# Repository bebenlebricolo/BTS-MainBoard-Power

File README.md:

# BTS-MainBoard-Power
Beer thermoregulation system mainboard  - power section

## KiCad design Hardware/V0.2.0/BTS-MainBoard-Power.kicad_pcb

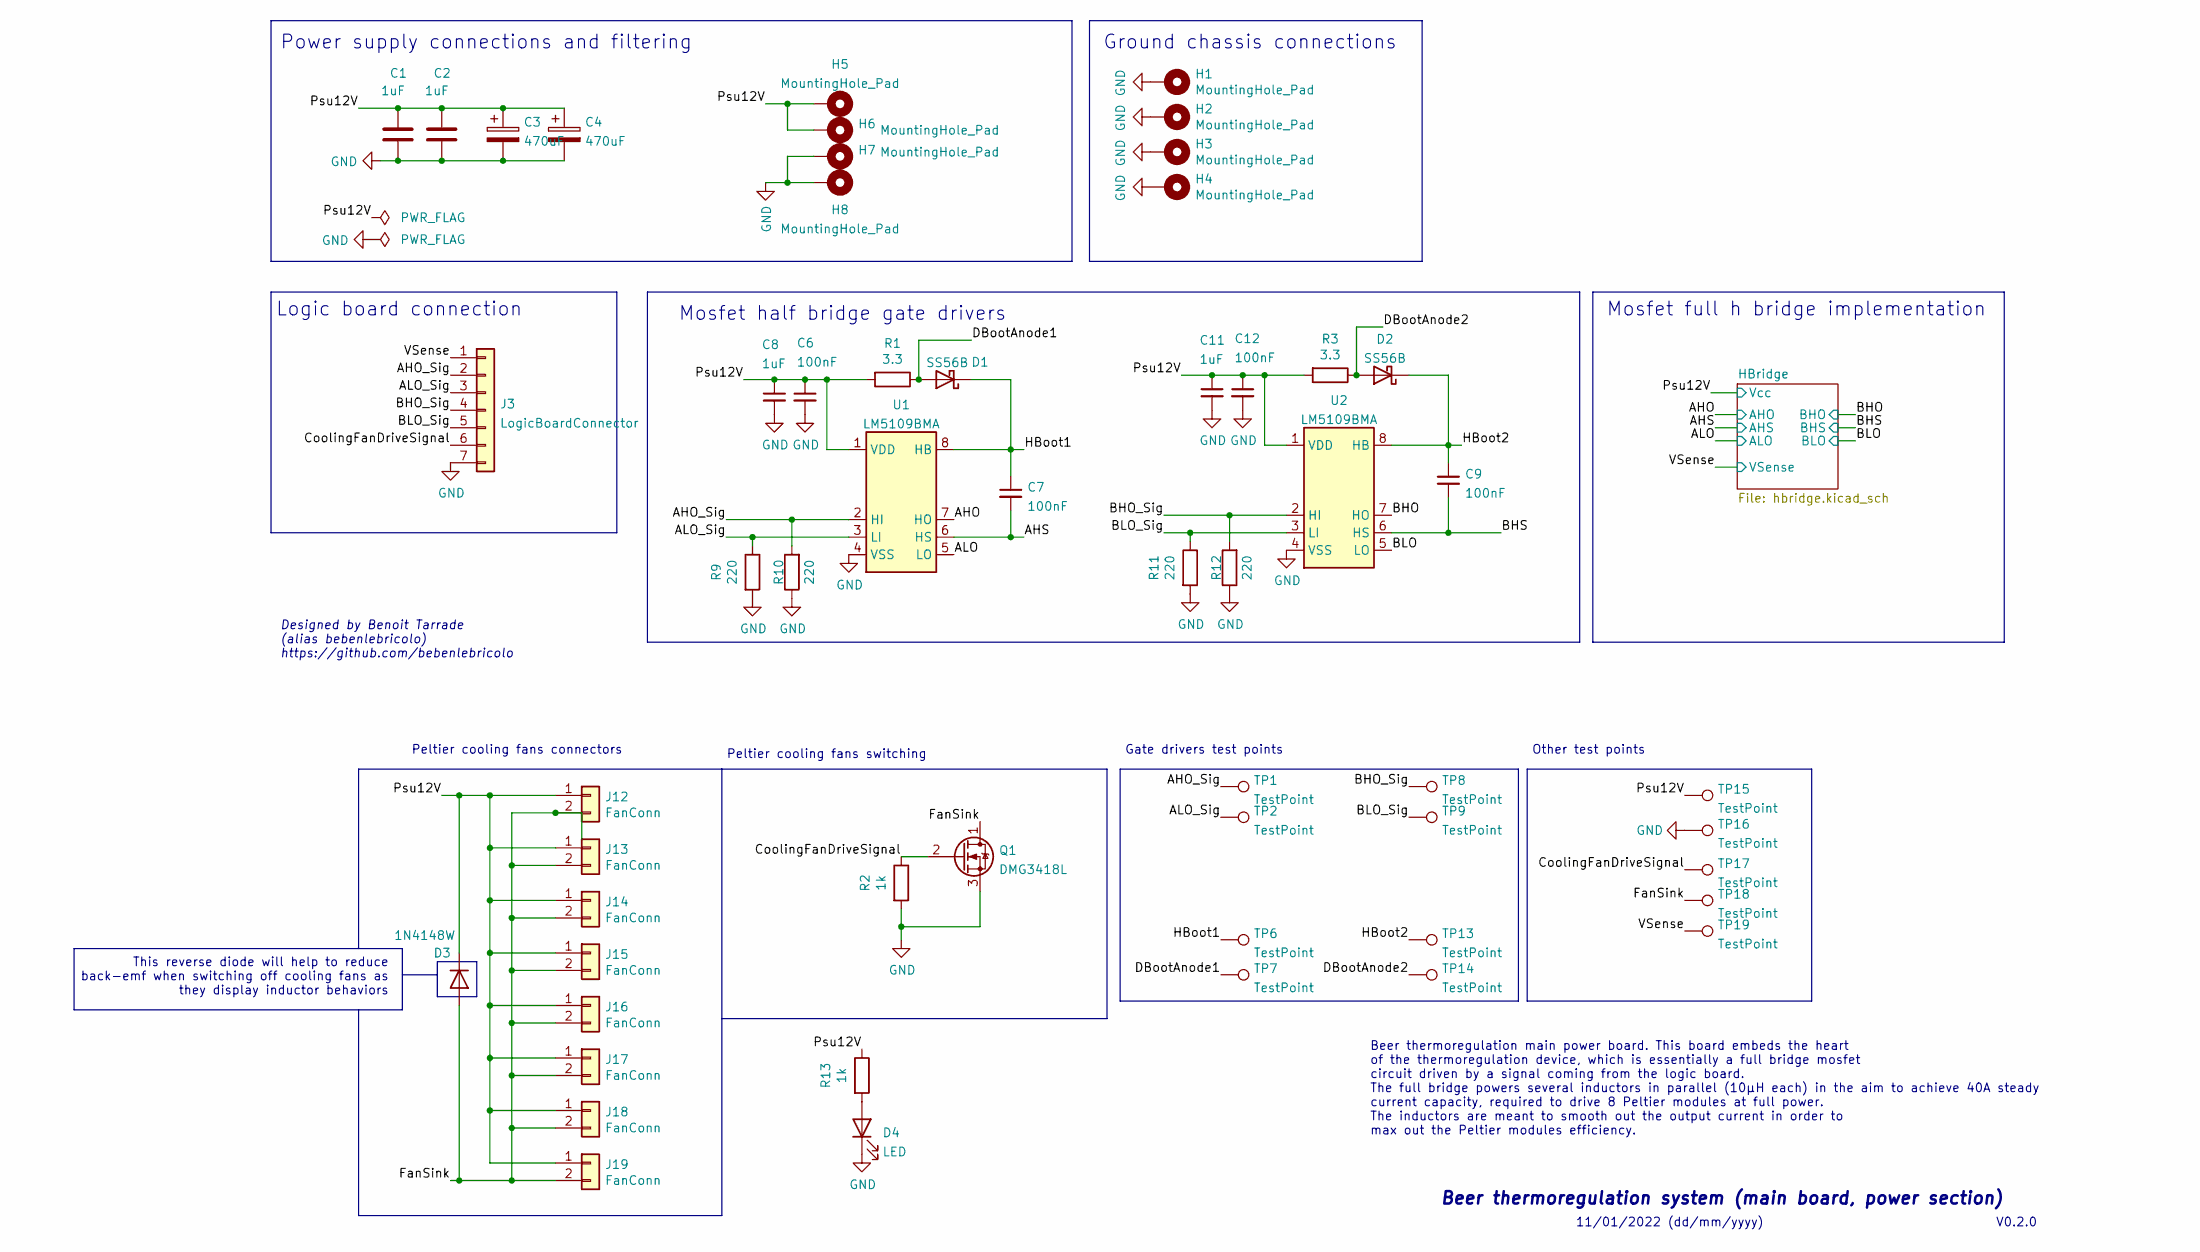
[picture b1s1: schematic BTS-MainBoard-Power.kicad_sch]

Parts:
C1, C2, C8, C11: 1uF; C_1206_3216Metric_Pad1.33x1.80mm_HandSolder
C3, C4: 470uF; CP_Elec_10x10
C6, C7, C9, C12: 100nF; C_1206_3216Metric_Pad1.33x1.80mm_HandSolder
D1, D2: SS56B
D3: 1N4148W; D_SOD-123
D4: LED; D_0805_2012Metric
H1, H2, H3, H4: MountingHole_Pad; MountingHole_4mm_Pad_Via
H5, H6, H7, H8: MountingHole_Pad; MountingHole_3mm_Pad_Via
J3: LogicBoardConnector; PinHeader_1x07_P2.54mm_Vertical
J12, J13, J14, J15, J16, J17, J18, J19: FanConn; PinSocket_1x02_P2.54mm_Vertical
Q1: DMG3418L; SOT-23
R1, R3: 3.3; R_1206_3216Metric_Pad1.30x1.75mm_HandSolder
R2, R13: 1k; R_1206_3216Metric_Pad1.30x1.75mm_HandSolder
R9, R10, R11, R12: 220; R_1206_3216Metric_Pad1.30x1.75mm_HandSolder
TP1, TP2, TP6, TP7, TP8, TP9, TP13, TP14, TP15, TP16, TP17, TP18, TP19: TestPoint; TestPoint_Pad_D1.0mm
U1, U2: LM5109BMA; SOIC-8_3.9x4.9mm_P1.27mm

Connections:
/AHO: U1.7 (HO); also elsewhere on the board
/AHO_Sig: J3.2, R10.2, TP1.1, U1.2 (HI)
/AHS: C7.2, U1.6 (HS); also elsewhere on the board
/ALO: U1.5 (LO); also elsewhere on the board
/ALO_Sig: J3.3, R9.1, TP2.1, U1.3 (LI)
/BHO: U2.7 (HO); also elsewhere on the board
/BHO_Sig: J3.4, R12.2, TP8.1, U2.2 (HI)
/BHS: C9.2, U2.6 (HS); also elsewhere on the board
/BLO: U2.5 (LO); also elsewhere on the board
/BLO_Sig: J3.5, R11.1, TP9.1, U2.3 (LI)
/CoolingFanDriveSignal: J3.6, Q1.2 (G), R2.1, TP17.1
/DBootAnode1: D1.2 (A), R1.1, TP7.1
/DBootAnode2: D2.2 (A), R3.1, TP14.1
/FanSink: D3.2 (A), J12.2, J13.2, J14.2, J15.2, J16.2, J17.2, J18.2, J19.2, Q1.1 (D), TP18.1
/HBoot1: C7.1, D1.1 (K), TP6.1, U1.8 (HB)
/HBoot2: C9.1, D2.1 (K), TP13.1, U2.8 (HB)
/Psu12V: C1.1, C2.1, C3.1, C4.1, C6.1, C8.1, C11.1, C12.1, D3.1 (K), H5.1, H6.1, J12.1, J13.1, J14.1, J15.1, J16.1, J17.1, J18.1, J19.1, R1.2, R3.2, R13.1, TP15.1, U1.1 (VDD), U2.1 (VDD); also elsewhere on the board
/VSense: J3.1, TP19.1; also elsewhere on the board
GND: C1.2, C2.2, C3.2, C4.2, C6.2, C8.2, C11.2, C12.2, D4.1 (K), H1.1, H2.1, H3.1, H4.1, H7.1, H8.1, J3.7, Q1.3 (S), R2.2, R9.2, R10.1, R11.2, R12.1, TP16.1, U1.4 (VSS), U2.4 (VSS); also elsewhere on the board
unnamed: D4.2 (A), R13.2

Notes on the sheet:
Peltier cooling fans connectors
Gate drivers test points
Logic board connection
Other test points
This reverse diode will help to reduce back-emf when switching off cooling fans as they display inductor behaviors
Mosfet half bridge gate drivers
Designed by Benoit Tarrade (alias bebenlebricolo) https://github.com/bebenlebricolo
11/01/2022 (dd/mm/yyyy)
Ground chassis connections
Peltier cooling fans switching
Mosfet full h bridge implementation
Power supply connections and filtering
V0.2.0
Beer thermoregulation main power board. This board embeds the heart of the thermoregulation device, which is essentially a full bridge mosfet circuit driven by a signal coming from the logic board. The full bridge powers several inductors in parallel (10µH each) in the aim to achieve 40A steady cur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
Beer thermoregulation system (main board, power section)

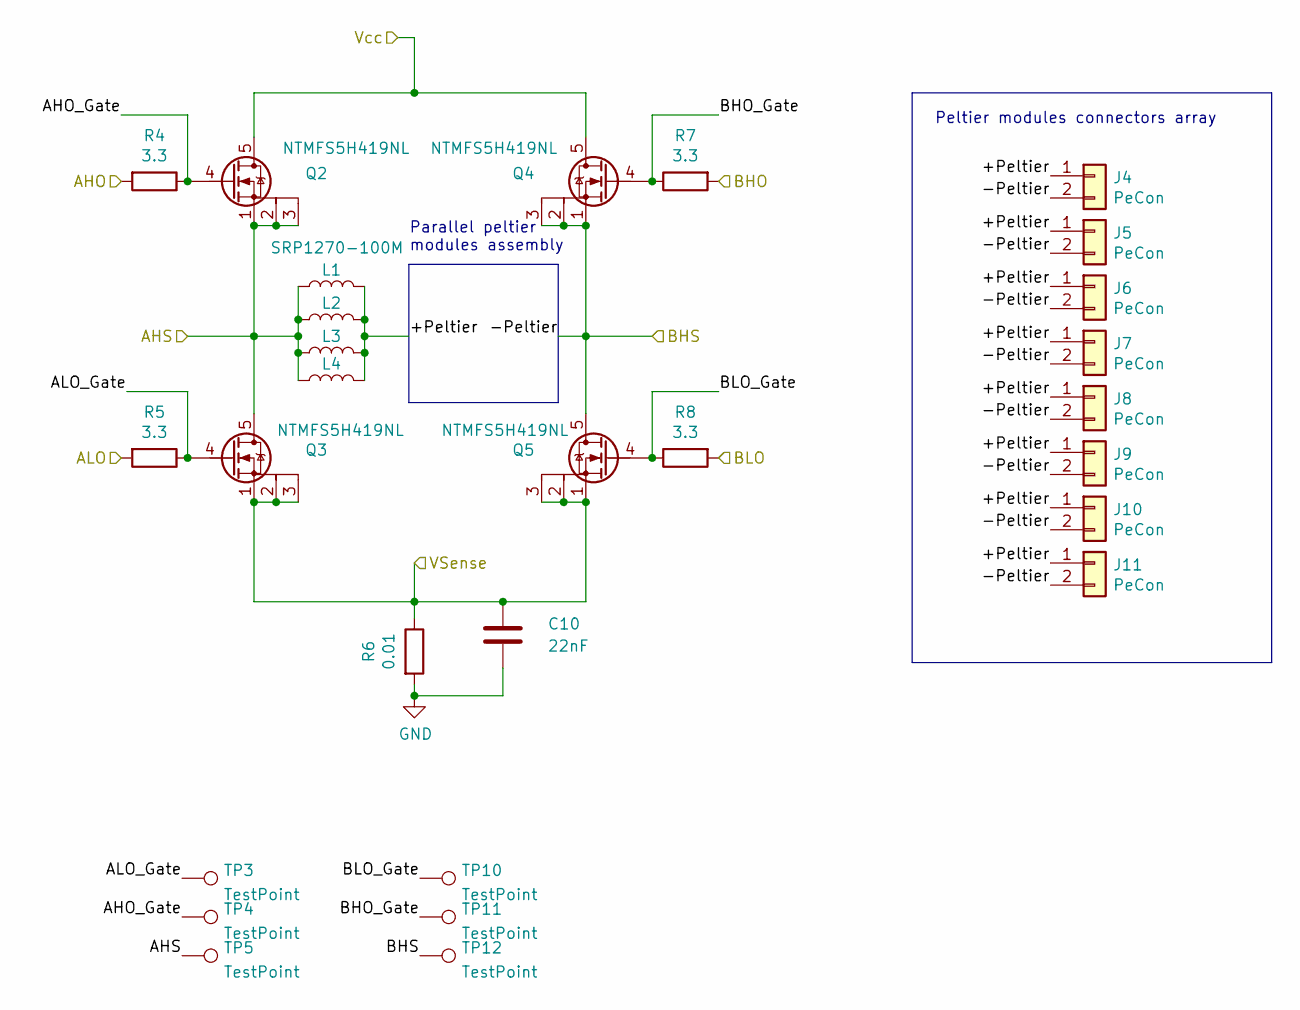
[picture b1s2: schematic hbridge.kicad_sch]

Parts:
C10: 22nF; C_1210_3225Metric_Pad1.33x2.70mm_HandSolder
J4, J5, J6, J7, J8, J9, J10, J11: PeCon; TE_1-1123723-2_1x02_P3.96mm_8Amps_Vertical
L1, L2, L3, L4: SRP1270-100M; L_Bourns_SRP1270
Q2, Q3, Q4, Q5: NTMFS5H419NL; NTMFS5G419NL
R4, R5, R7, R8: 3.3; R_1206_3216Metric_Pad1.30x1.75mm_HandSolder
R6: 0.01; R_2512_6332Metric_Pad1.40x3.35mm_HandSolder
TP3, TP4, TP5, TP10, TP11, TP12: TestPoint; TestPoint_Pad_D1.0mm

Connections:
/AHO: R4.2; also elsewhere on the board
/AHS: L1.1, L2.1, L3.1, L4.1, Q2.1 (S), Q2.2 (S), Q2.3 (S), Q3.5 (D), TP5.1; also elsewhere on the board
/ALO: R5.2; also elsewhere on the board
/BHO: R7.2; also elsewhere on the board
/BHS: J4.2, J5.2, J6.2, J7.2, J8.2, J9.2, J10.2, J11.2, Q4.1 (S), Q4.2 (S), Q4.3 (S), Q5.5 (D), TP12.1; also elsewhere on the board
/BLO: R8.2; also elsewhere on the board
/HBridge/+Peltier: J4.1, J5.1, J6.1, J7.1, J8.1, J9.1, J10.1, J11.1, L1.2, L2.2, L3.2, L4.2
/HBridge/AHO_Gate: Q2.4 (G), R4.1, TP4.1
/HBridge/ALO_Gate: Q3.4 (G), R5.1, TP3.1
/HBridge/BHO_Gate: Q4.4 (G), R7.1, TP11.1
/HBridge/BLO_Gate: Q5.4 (G), R8.1, TP10.1
/Psu12V: Q2.5 (D), Q4.5 (D); also elsewhere on the board
/VSense: C10.1, Q3.1 (S), Q3.2 (S), Q3.3 (S), Q5.1 (S), Q5.2 (S), Q5.3 (S), R6.1; also elsewhere on the board
GND: C10.2, R6.2; also elsewhere on the board

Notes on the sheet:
Parallel peltier modules assembly
Peltier modules connectors array

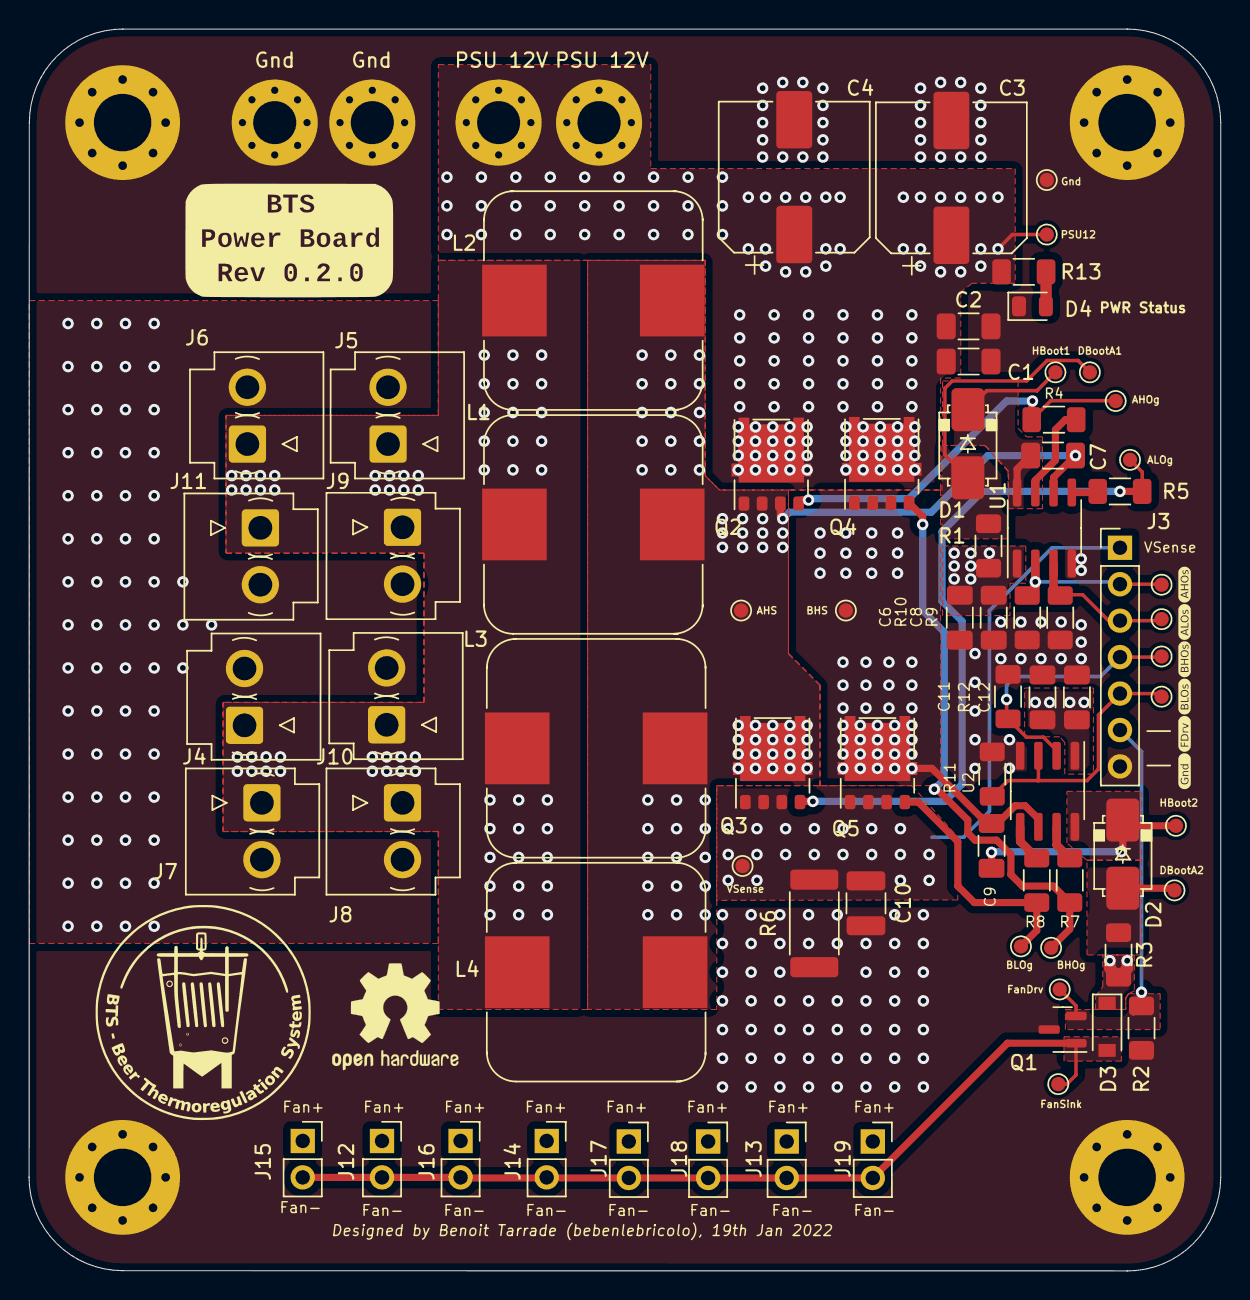
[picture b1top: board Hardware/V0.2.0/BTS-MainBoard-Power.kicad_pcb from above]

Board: 4 copper layers, 83.0 x 86.5 mm, 83 parts (0 on the bottom side), 25 nets.

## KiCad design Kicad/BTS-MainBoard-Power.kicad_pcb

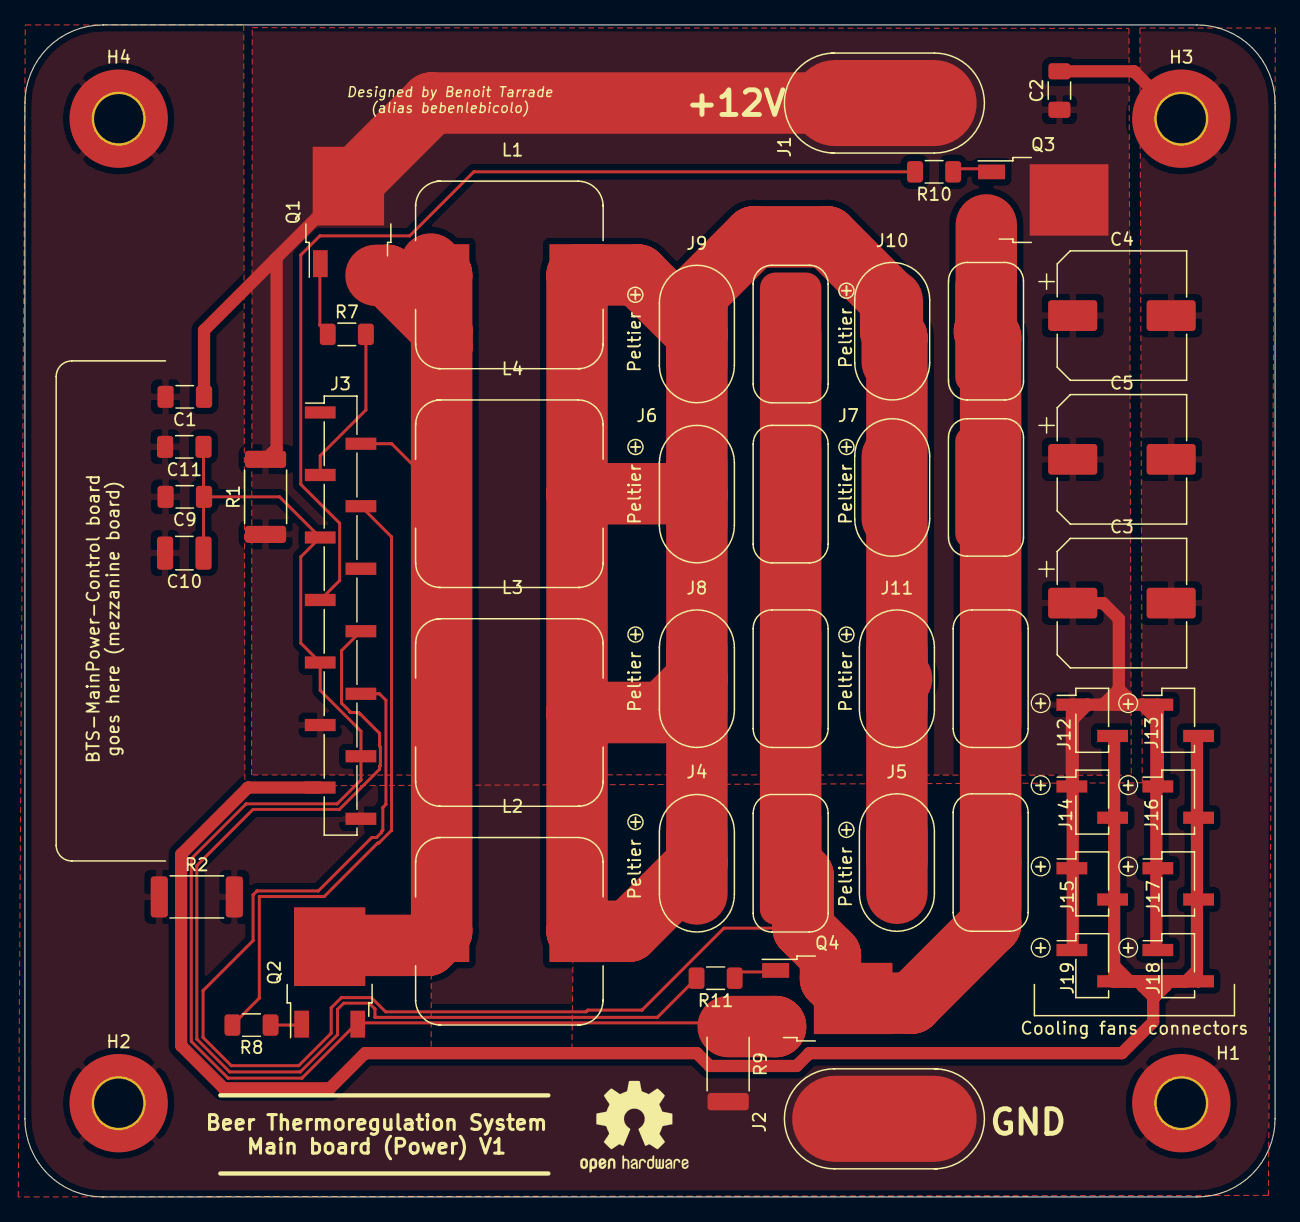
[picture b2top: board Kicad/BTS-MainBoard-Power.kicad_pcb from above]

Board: 2 copper layers, 101.6 x 95.3 mm, 46 parts (0 on the bottom side), 15 nets.

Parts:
C1, C2: 100nF; C_1206_3216Metric_Pad1.33x1.80mm_HandSolder
C3, C4, C5: 470uF; CP_Elec_10x10
C9, C11: 1nF; C_1206_3216Metric_Pad1.33x1.80mm_HandSolder
C10: 22nF; C_1210_3225Metric_Pad1.33x2.70mm_HandSolder
H1, H2, H3, H4: MountingHole_Pad; MountingHole_4mm_Pad_TopOnly
J1: +12VIn; Power_Solder_Pad_7x15mm
J2: GNDIn; Power_Solder_Pad_7x15mm
J3: Conn_01x14; PinHeader_1x14_P2.54mm_Vertical_SMD_Pin1Left
J4, J5, J6, J7, J8, J9, J10, J11: Conn_01x02; Power_Solder_Pad_5x10mm_02
J12, J13, J14, J15, J16, J17, J18, J19: Conn_01x02; PinHeader_1x02_P2.54mm_Vertical_SMD_Pin1Left
L1, L2, L3, L4: SRP1270-100M; L_Bourns_SRP1270
Q1, Q2, Q3, Q4: STD80N6F6; TO-252-2
R1, R2: 0; R_2512_6332Metric_Pad1.40x3.35mm_HandSolder
R7, R8, R10, R11: 3.3; R_1206_3216Metric_Pad1.30x1.75mm_HandSolder
R9: 0.01; R_2512_6332Metric_Pad1.40x3.35mm_HandSolder

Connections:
+12V: C1.1, C2.1, C3.1, C4.1, C5.1, J1.1, J3.11, J12.1, J13.1, J14.1, J15.1, J16.1, J17.1, J18.1, J19.1, Q1.2, Q3.2, R1.1, R1.2
/AHO: J3.3, R7.2
/AHS: J3.2, L1.1, L2.1, L3.1, L4.1, Q1.3, Q2.2
/ALO: J3.4, R8.2
/ALS: C9.1, C10.1, C11.1, J3.5, J3.9, J3.12, Q2.3, Q4.3, R9.1
/BHO: J3.7, R10.2
/BHS: J3.10, J4.2, J5.2, J6.2, J7.2, J8.2, J9.2, J10.2, J11.2, Q3.3, Q4.2
/BLO: J3.8, R11.2
/FanDrive: J3.13, J12.2, J13.2, J14.2, J15.2, J16.2, J17.2, J18.2, J19.2
/PeltierLeft: J4.1, J5.1, J6.1, J7.1, J8.1, J9.1, J10.1, J11.1, L1.2, L2.2, L3.2, L4.2
GND: C1.2, C2.2, C3.2, C4.2, C5.2, C9.2, C10.2, C11.2, H1.1, H2.1, H3.1, H4.1, J2.1, J3.14, R2.1, R2.2, R9.2
unnamed: Q1.1, R7.1
unnamed: Q2.1, R8.1
unnamed: Q3.1, R10.1
unnamed: Q4.1, R11.1

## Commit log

2021-09-10 Initial commit, main board design is pending
2021-09-10 Modified silkscreen and added cooling fans connectors
2021-09-10 Updated schematic and silkscreen
2021-09-10 Added mezzanine footprint
2021-09-10 Almost finalized designing single board
2021-09-10 Moved kicad files into Kicad folder
2021-09-10 Moved some simulations into BTS-LogicBoard
2021-09-13 Moved libraries
2021-10-05 Renamed Libraries and renamed project files as well
2021-10-05 Replotted gerber files
2021-10-05 Updated board with FANDRIVE power signal and silkscreen
2021-10-05 Updated BOM
2021-10-05 Created BOM
2021-10-05 Sent files to fab
2021-10-06 Moved BOM out of Kicad folder
2022-01-08 Migrated kicad files to version 6
2022-01-08 Moved hardware design to its dedicated folder (v0.1.0) and updated notes and readmes
2022-01-08 Fixed readme screenshot not displaying
2022-01-11 Started to redesign the schematic
2022-01-13 Added new footprints and components libraries
2022-01-13 Started first routing steps
2022-01-14 Improved zoning thermal layout
2022-01-17 Rewired the whole PCB with much more compact design
2022-01-17 Finished routing, now needs improvements
2022-01-17 Redid edge cuts
2022-01-17 Improved a bit tracks
2022-01-19 Updated the board with logo and silkscreen improvements
2022-01-19 Updated silkscreen and extended BHS zone to the edge of the board
2022-01-20 Reduced vias count, there were too many in there
2022-01-20 Added some drawings
2022-01-20 Moved Libraries and improved graphics
2022-01-20 Moved drawings around
2022-01-20 Exported BOMS
2022-01-20 Exported Gerbers and sent board to fab
2022-01-20 Added screenshots and updated Readme a little bit
